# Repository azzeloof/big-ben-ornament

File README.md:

# Big Ben Ornament
 A PCB ornament/desk toy complete with an E-Paper display!

## Hardware
Okay, so this is a bit overkill for an ornament. It uses an ATmega328P to coordinate a Real-Time Clock, some RAM, and the driver circuitry for an E-Paper display. The end result is a pretty damn good looking (and accurate) clock. 
There are several problems- I never connected AVCC on the ATmega, the RESET pin was connected incorrectly, and a transistor in the EPD driver circuit was laid out with the incorrect footprint. My brother helped me resolve all this with some clever bodge, but it would probably be best to actually design the boards properly for future versions.

## Firmware
The clock's firmware is just an Arduino sketch. It requires the Waveshare EPD library, as well as Adafruit's RTClib. The clock face is a bitmap stored in memory, and the hands are dynamically drawn from lines and circles. 
To program the chips, I flashed the arduino bootloader onto the chip and used the ["breadboard Arduino" board file](https://www.arduino.cc/en/Tutorial/BuiltInExamples/ArduinoToBreadboard). I programmed the board with SparkFun's [Pocket AVR Programmer](https://www.sparkfun.com/products/9825), but you should be able to use any programmer compatibe with the ATmega328P (or just use an Arduino Uno!).

## Version History
Release 1.0 will represent the bus ornaments as we initially made and distributed them. Once it is released, maybe we'll improve some stuff (but any hardware improvements will be untested).

## Warning
Electricity creates heat, and excess heat around something like a Christmas tree can cause big problems. Use at your own risk! The designs here have only been minimally tested and are absolutley not guarenteed to be safe.

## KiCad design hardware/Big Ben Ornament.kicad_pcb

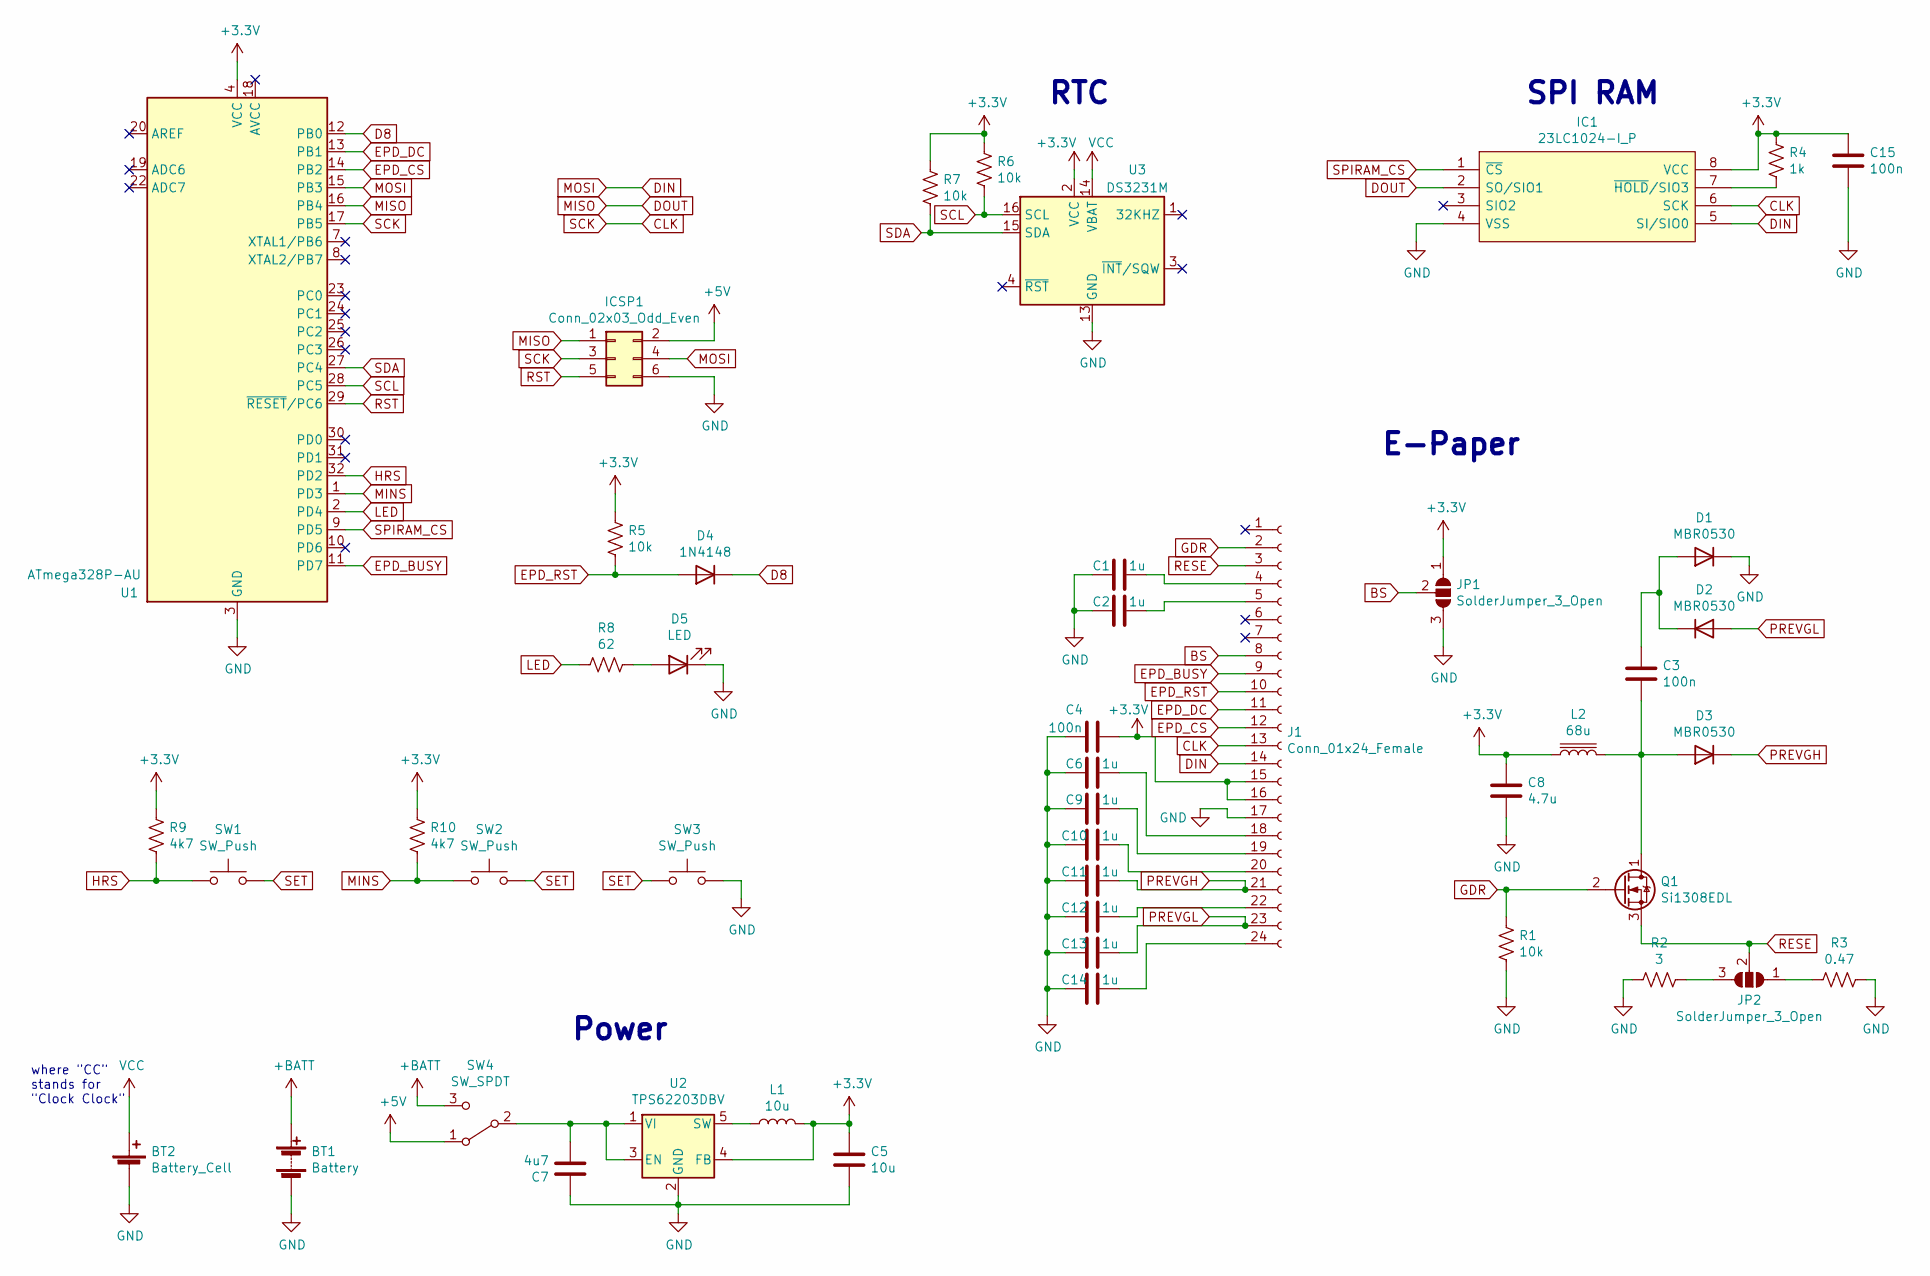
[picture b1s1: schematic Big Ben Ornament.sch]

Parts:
BT1: Battery; BatteryHolder_Keystone_3002_1x2032
BT2: Battery_Cell; BatteryHolder_Keystone_3000_1x12mm
C1, C2, C6, C9, C10, C11, C12, C13, C14: 1u; C_0805_2012Metric_Pad1.18x1.45mm_HandSolder; Voltage 50
C3: 100n; C_0805_2012Metric_Pad1.18x1.45mm_HandSolder; Voltage 50
C4, C15: 100n; C_0805_2012Metric_Pad1.18x1.45mm_HandSolder
C5: 10u; C_0805_2012Metric_Pad1.18x1.45mm_HandSolder
C7: 4u7; C_0805_2012Metric_Pad1.18x1.45mm_HandSolder
C8: 4.7u; C_0805_2012Metric_Pad1.18x1.45mm_HandSolder
D1, D2, D3: MBR0530; D_SOD-123
D4: 1N4148; D_SOD-123
D5: LED; LED_0805_2012Metric
IC1: 23LC1024-I_P; SOIC-8_3.9x4.9mm_P1.27mm; Mouser Part Number 579-23LC1024-I/P
ICSP1: Conn_02x03_Odd_Even; PinHeader_2x03_P2.54mm_Vertical_SMD
J1: Conn_01x24_Female; TE_2-1734839-4_1x24-1MP_P0.5mm_Horizontal
JP1, JP2: SolderJumper_3_Open; SolderJumper-3_P1.3mm_Open_RoundedPad1.0x1.5mm
L1: 10u; L_Coilcraft_XAL60xx_6.36x6.56mm
L2: 68u; L_Coilcraft_XxL4040
Q1: Si1308EDL; SOT-323_SC-70_Handsoldering
R1, R5, R6, R7: 10k; R_0805_2012Metric_Pad1.20x1.40mm_HandSolder
R2: 3; R_0805_2012Metric_Pad1.20x1.40mm_HandSolder
R3: 0.47; R_0805_2012Metric_Pad1.20x1.40mm_HandSolder
R4: 1k; R_0805_2012Metric_Pad1.20x1.40mm_HandSolder
R8: 62; R_0805_2012Metric_Pad1.20x1.40mm_HandSolder
R9, R10: 4k7; R_0805_2012Metric_Pad1.20x1.40mm_HandSolder
SW1, SW2, SW3: SW_Push; SW_Push_1P1T_NO_CK_KSC6xxJ
SW4: SW_SPDT; SW_SPDT_PCM12
U1: ATmega328P-AU; TQFP-32_7x7mm_P0.8mm
U2: TPS62203DBV; SOT-23-5
U3: DS3231M; SOIC-16W_7.5x10.3mm_P1.27mm

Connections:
+3V3: C4.2, C5.1, C8.1, C15.1, IC1.8 (VCC), J1.15, J1.16, JP1.1 (A), L1.2, L2.1, R4.2, R5.1, R6.1, R7.1, R9.2, R10.2, U1.4 (VCC), U1.6 (VCC), U2.4 (FB), U3.2 (VCC)
+5V: ICSP1.2, SW4.1 (A); also elsewhere on the board
+BATT: BT1.1 (+), SW4.3 (C)
BS: J1.8, JP1.2 (C)
CLK: IC1.6 (SCK), ICSP1.3, J1.13, U1.17 (PB5); also elsewhere on the board
D8: D4.1 (K), U1.12 (PB0)
DIN: IC1.5 (SI/SIO0), ICSP1.4, J1.14, U1.15 (PB3); also elsewhere on the board
DOUT: IC1.2 (SO/SIO1), ICSP1.1, U1.16 (PB4); also elsewhere on the board
EPD_BUSY: J1.9, U1.11 (PD7)
EPD_CS: J1.12, U1.14 (PB2)
EPD_DC: J1.11, U1.13 (PB1)
EPD_RST: D4.2 (A), J1.10, R5.2
GDR: J1.2, Q1.2 (G), R1.1
GND: BT1.2 (-), BT2.2 (-), C1.2, C2.1, C4.1, C5.2, C6.1, C7.1, C8.2, C9.1, C10.1, C11.1, C12.1, C13.1, C14.1, C15.2, D1.1 (K), D5.1 (K), IC1.4 (VSS), ICSP1.6, J1.17, JP1.3 (B), R1.2, R2.1, R3.2, SW3.2, U1.3 (GND), U1.5 (GND), U1.21 (GND), U2.2 (GND), U3.5 (GND), U3.6 (GND), U3.7 (GND), U3.8 (GND), U3.9 (GND), U3.10 (GND), U3.11 (GND), U3.12 (GND), U3.13 (GND); also elsewhere on the board
HRS: R9.1, SW1.1, U1.32 (PD2)
LED: R8.2, U1.2 (PD4)
MINS: R10.1, SW2.1, U1.1 (PD3)
unnamed: C1.1, J1.4
unnamed: C2.2, J1.5
unnamed: C3.1, D1.2 (A), D2.1 (K)
unnamed: C3.2, D3.2 (A), L2.2, Q1.1 (D)
unnamed: C6.2, J1.18
unnamed: C7.2, SW4.2 (B), U2.1 (VI), U2.3 (EN)
unnamed: C9.2, J1.19
unnamed: C10.2, J1.20
unnamed: C12.2, J1.22
unnamed: C14.2, J1.24
unnamed: D5.2 (A), R8.1
unnamed: IC1.7 (~HOLD~/SIO3), R4.1
unnamed: JP2.1 (A), R3.1
unnamed: JP2.3 (B), R2.2
unnamed: L1.1, U2.5 (SW)
PREVGH: C11.2, D3.1 (K), J1.21
PREVGL: C13.2, D2.2 (A), J1.23
RESE: J1.3, JP2.2 (C), Q1.3 (S)
RST: ICSP1.5, U1.29 (~RESET~/PC6); also elsewhere on the board
SCL: R6.2, U1.28 (PC5), U3.16 (SCL)
SDA: R7.2, U1.27 (PC4), U3.15 (SDA)
SET: SW1.2, SW2.2, SW3.1
SPIRAM_CS: IC1.1 (~CS), U1.9 (PD5)
VCC: BT2.1 (+), U3.14 (VBAT)

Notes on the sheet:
SPI RAM
Power
E-Paper
RTC
where "CC" stands for "Clock Clock"

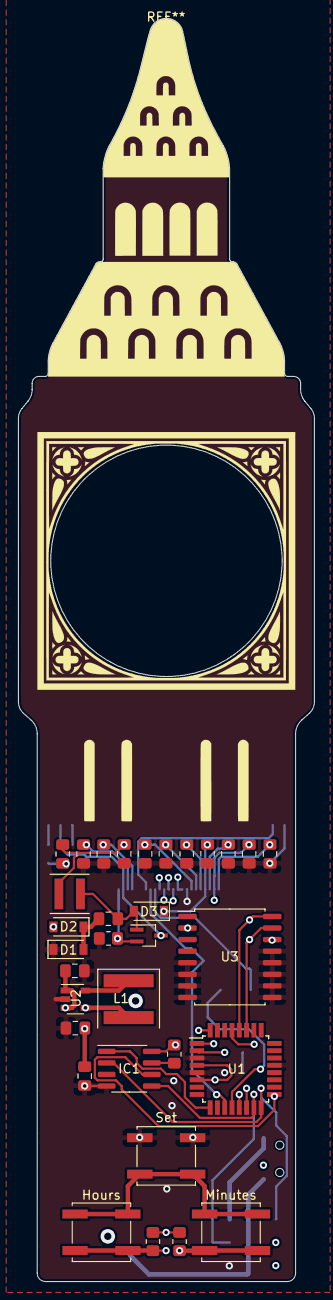
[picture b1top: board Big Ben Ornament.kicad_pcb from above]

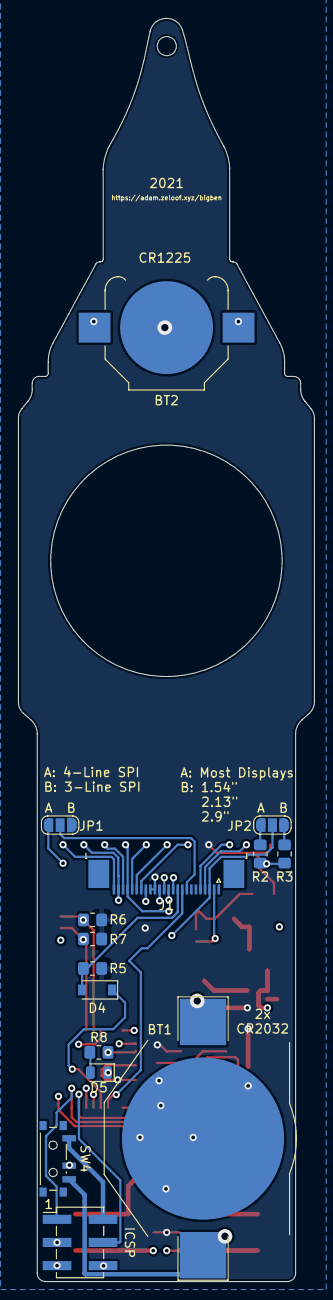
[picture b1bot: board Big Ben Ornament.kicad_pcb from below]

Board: 4 copper layers, 32.5 x 138.7 mm, 47 parts (15 on the bottom side), 41 nets.

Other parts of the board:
ICSP: Conn_02x03_Odd_Even; PinHeader_2x03_P2.54mm_Vertical_SMD

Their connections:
+5V: ICSP.2; also elsewhere on the board
CLK: ICSP.3; also elsewhere on the board
DIN: ICSP.4; also elsewhere on the board
DOUT: ICSP.1; also elsewhere on the board
GND: ICSP.6; also elsewhere on the board
RST: ICSP.5; also elsewhere on the board

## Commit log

2021-11-22 Layout finished, gerbers generated
2021-12-13 Commit prep
2021-12-17 started writing firmware
2021-12-17 firmware in progress
2021-12-18 It tells time!
2021-12-18 Slight code cleanup
2021-12-22 Firmware and documentation
2021-12-27 added HTML BOM
